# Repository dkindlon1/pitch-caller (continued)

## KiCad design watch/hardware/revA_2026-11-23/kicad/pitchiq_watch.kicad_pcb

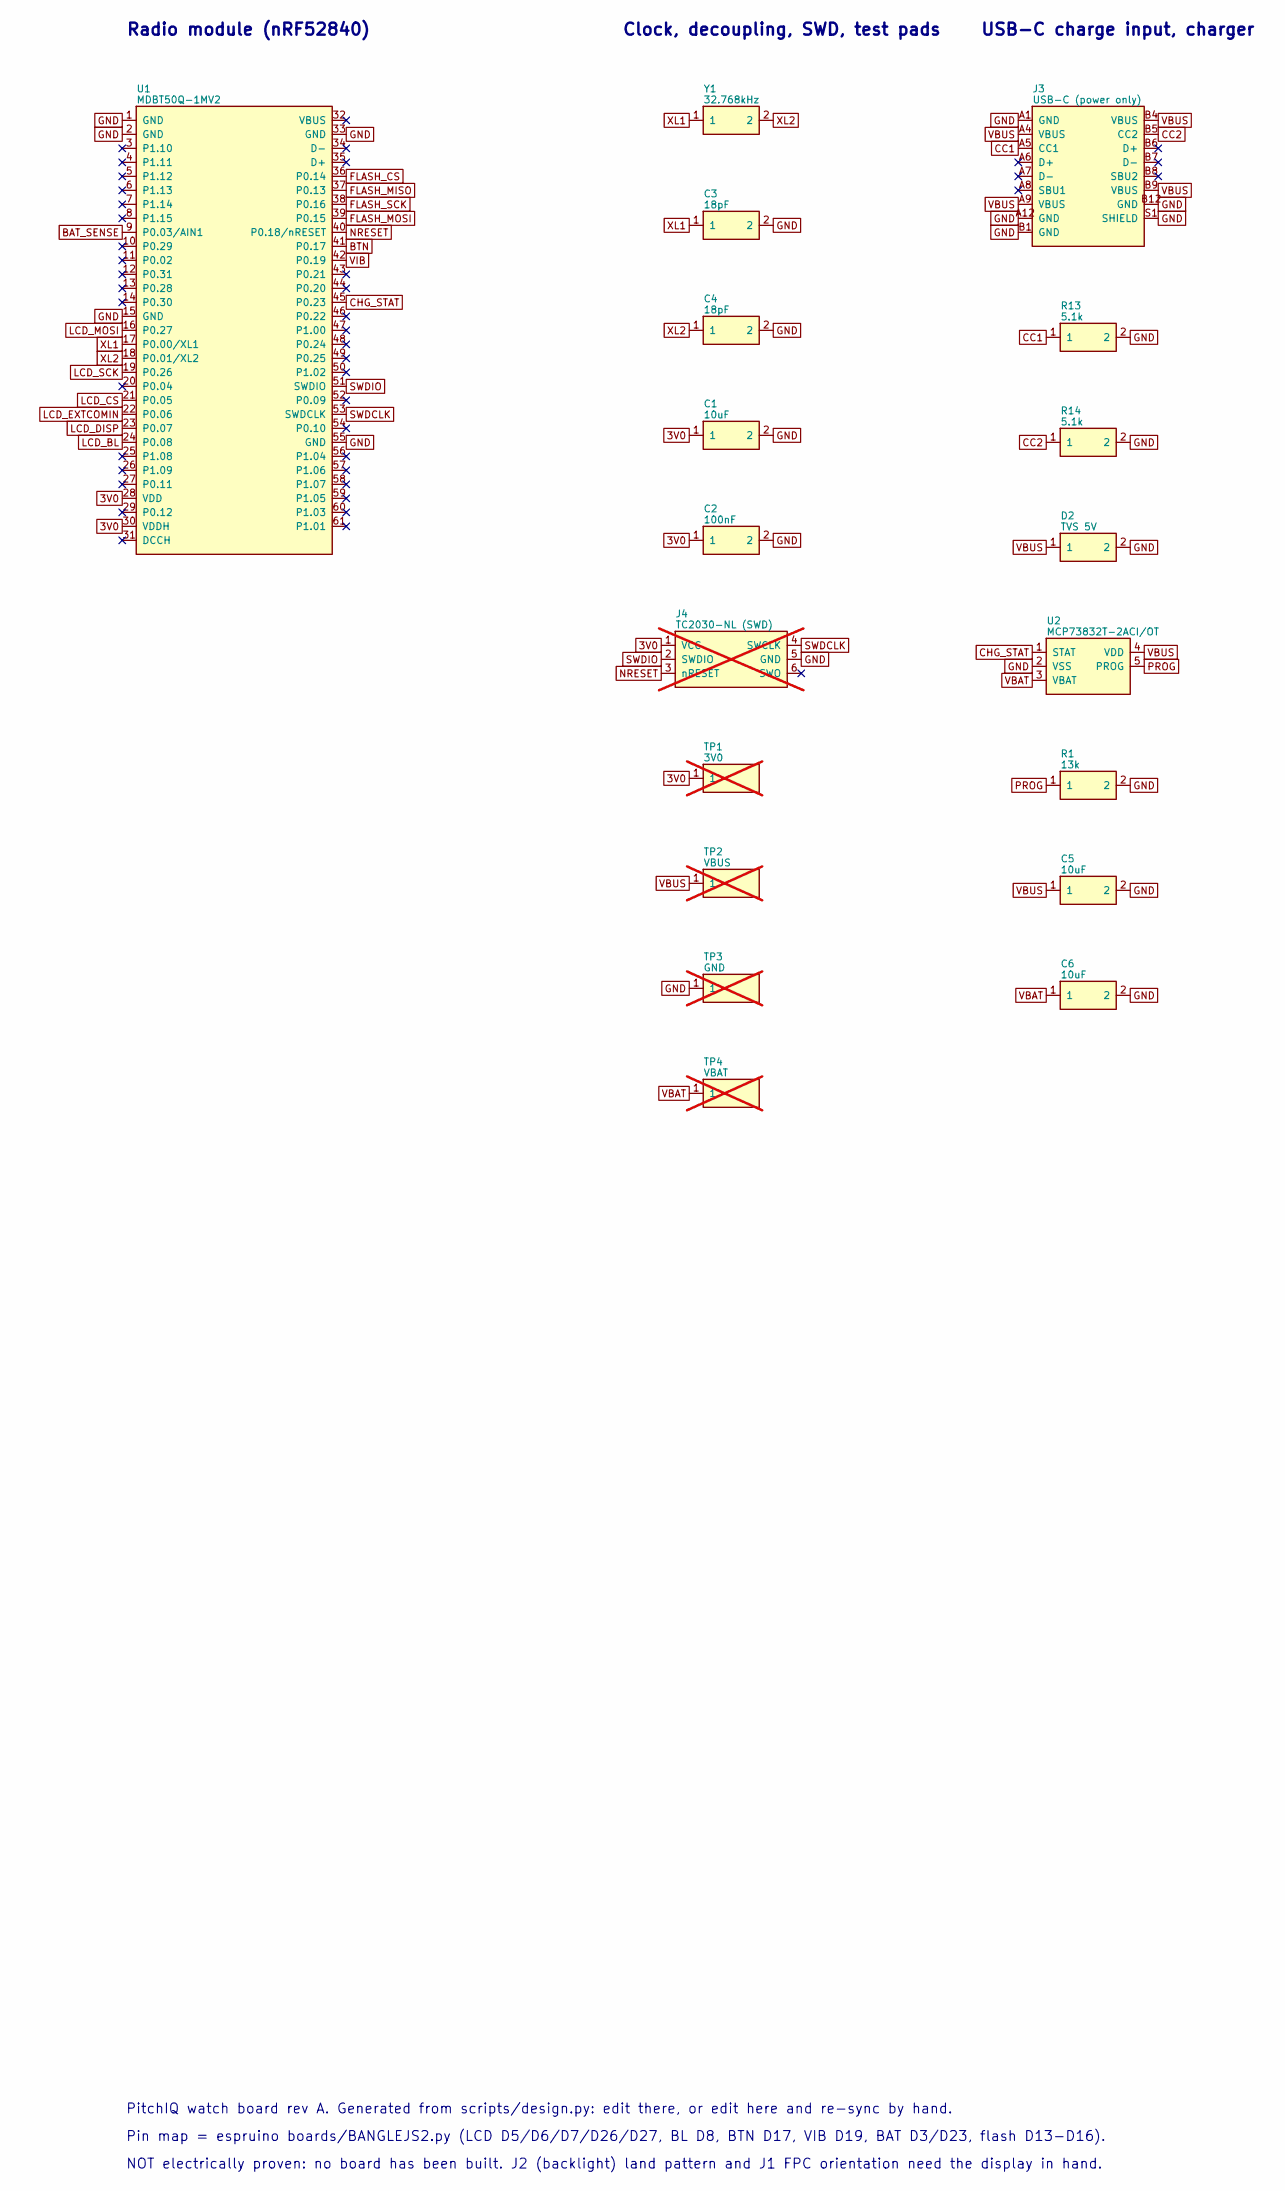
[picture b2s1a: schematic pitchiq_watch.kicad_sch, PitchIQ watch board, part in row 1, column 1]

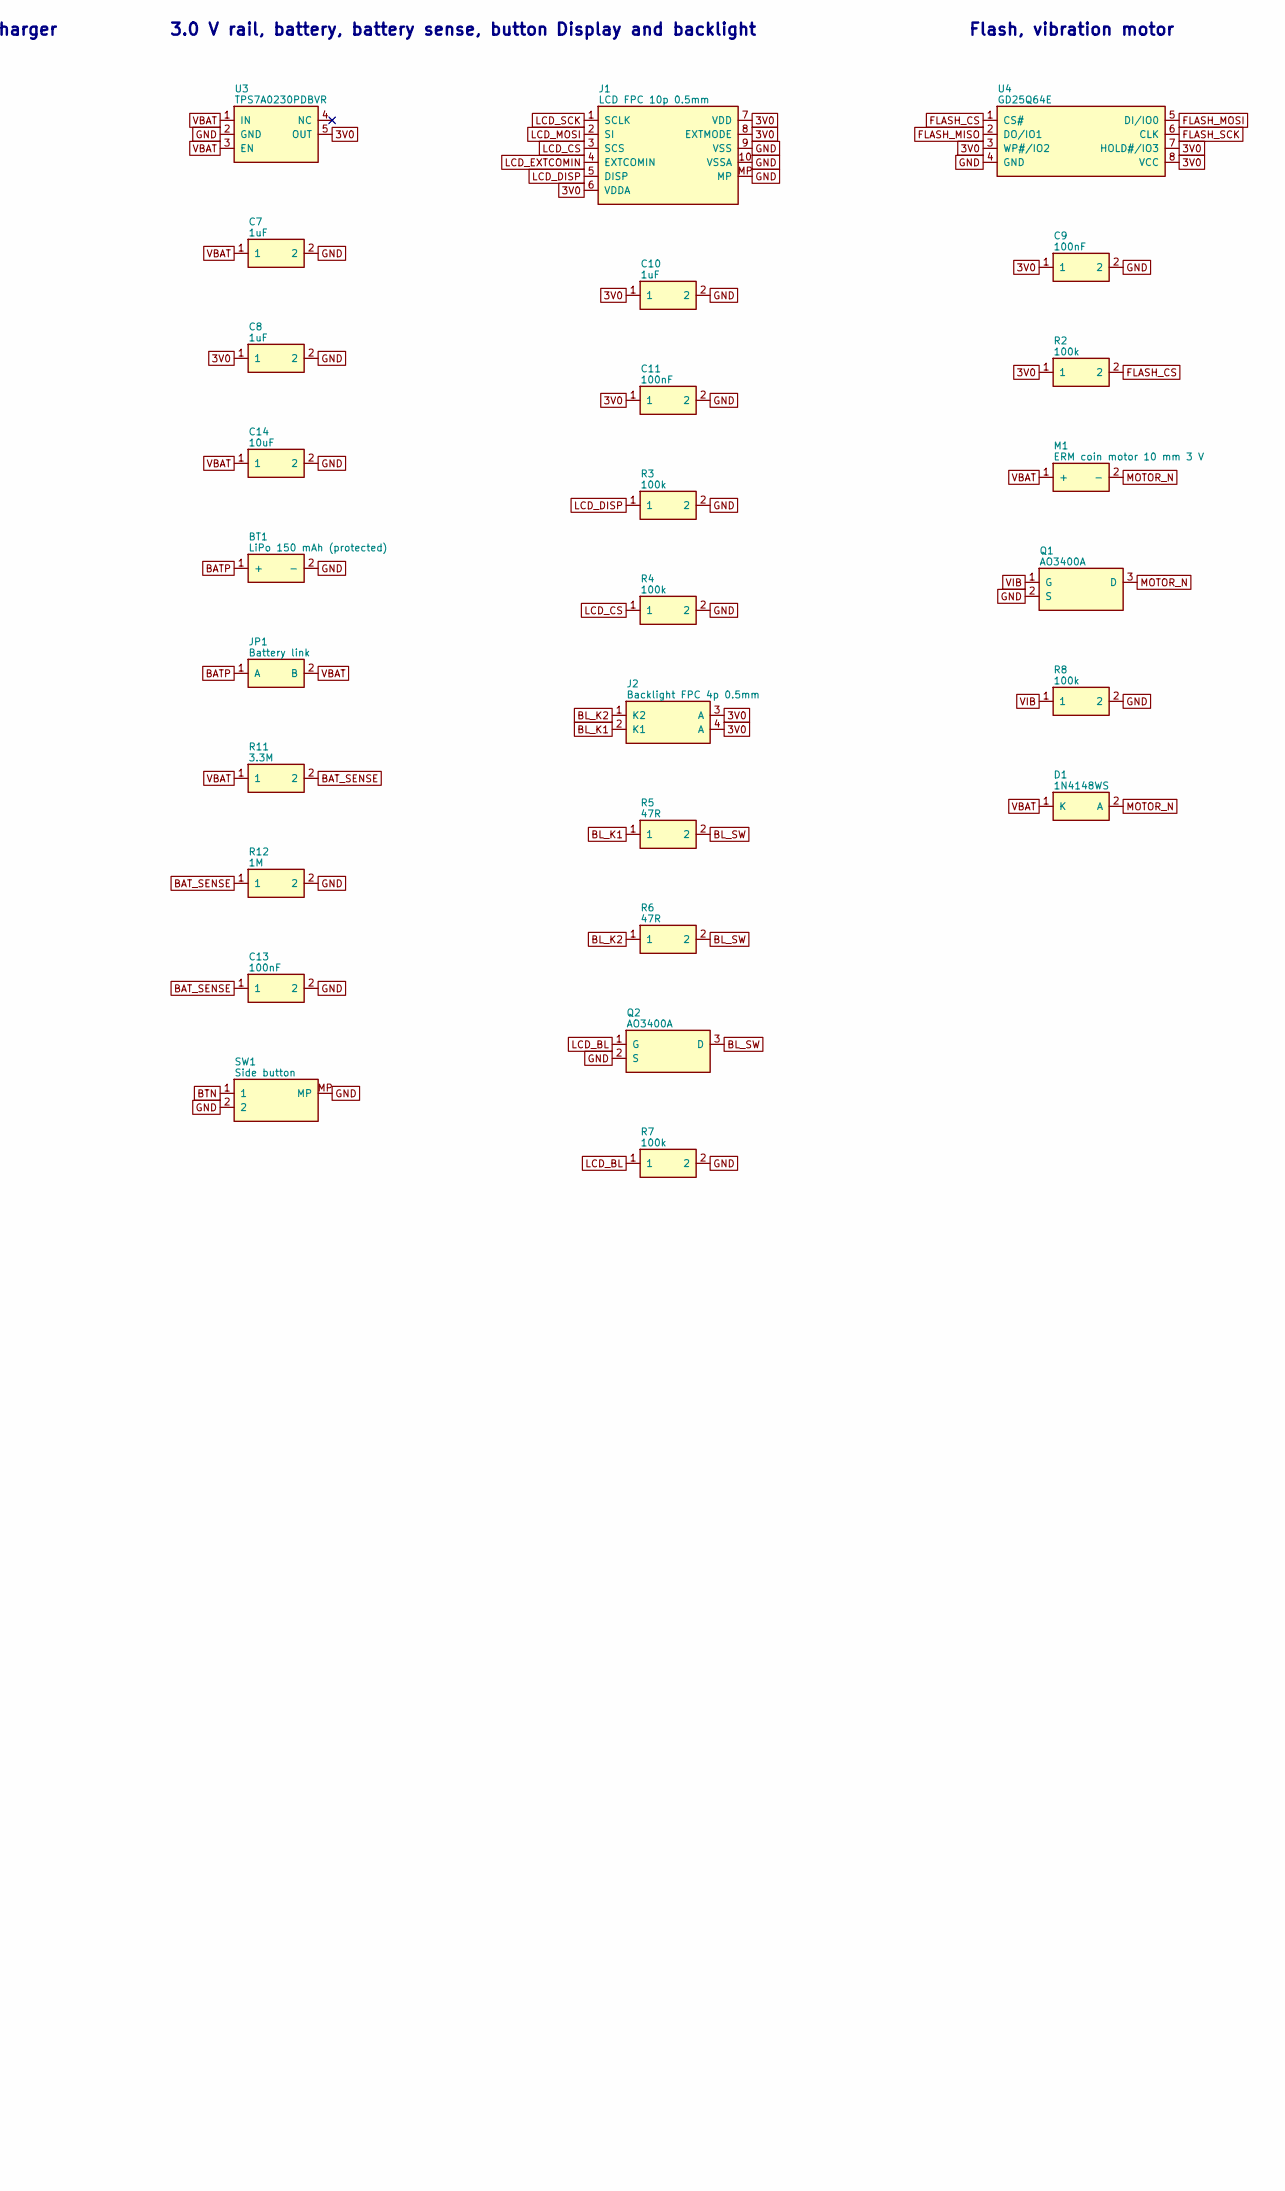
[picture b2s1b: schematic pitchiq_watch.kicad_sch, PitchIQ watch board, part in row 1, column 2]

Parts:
BT1: LiPo 150 mAh (protected); Pad_2x_wire; MPN 1317
C1, C5, C6, C14: 10uF; C_0603_1608Metric; MPN CL10A106KP8NNNC; LCSC C19702
C2, C9, C11, C13: 100nF; C_0402_1005Metric; MPN CL05B104KO5NNNC; LCSC C1525
C3, C4: 18pF; C_0402_1005Metric; MPN CL05C180JB5NNNC; LCSC C307443
C7, C8, C10: 1uF; C_0402_1005Metric; MPN CL05A105KA5NQNC; LCSC C52923
D1: 1N4148WS; D_SOD-323; MPN 1N4148WS; LCSC C2128
D2: TVS 5V; D_SOD-323; MPN PESD5V0S1BA; LCSC C2985486
J1: LCD FPC 10p 0.5mm; Hirose_FH12-10S-0.5SH_1x10-1MP_P0.50mm_Horizontal; MPN FH12-10S-0.5SH(55); LCSC C506791
J2: Backlight FPC 4p 0.5mm; FPC_4p_0.5mm_pads; MPN (pads only)
J3: USB-C (power only); USB_C_Receptacle_HRO_TYPE-C-31-M-12; MPN TYPE-C-31-M-12; LCSC C165948
J4: TC2030-NL (SWD); Tag-Connect_TC2030-IDC-NL_2x03_P1.27mm_Vertical; MPN (footprint only); not fitted
JP1: Battery link; SolderJumper-2_P1.3mm_Open_RoundedPad1.0x1.5mm; MPN (solder bridge)
M1: ERM coin motor 10 mm 3 V; Pad_2x_wire_small; MPN FIT0774
Q1, Q2: AO3400A; SOT-23; MPN AO3400A; LCSC C20917
R1: 13k; R_0402_1005Metric; MPN 0402WGF1302TCE; LCSC C25754
R2, R3, R4, R7, R8: 100k; R_0402_1005Metric; MPN 0402WGF1003TCE; LCSC C25741
R5, R6: 47R; R_0402_1005Metric; MPN 0402WGF470JTCE; LCSC C25118
R11: 3.3M; R_0402_1005Metric; MPN RC0402FR-073M3L; LCSC C470023
R12: 1M; R_0402_1005Metric; MPN 0402WGF1004TCE; LCSC C26083
R13, R14: 5.1k; R_0402_1005Metric; MPN 0402WGF5101TCE; LCSC C25905
SW1: Side button; SW_Push_1P1T-MP_NO_Horizontal_Alps_SKRTLAE010; MPN SKRTLAE010; LCSC C110293
TP1: 3V0; TestPoint_Pad_D1.5mm; not fitted
TP2: VBUS; TestPoint_Pad_D1.5mm; not fitted
TP3: GND; TestPoint_Pad_D1.5mm; not fitted
TP4: VBAT; TestPoint_Pad_D1.5mm; not fitted
U1: MDBT50Q-1MV2; Raytac_MDBT50Q; MPN MDBT50Q-1MV2; LCSC C5118826
U2: MCP73832T-2ACI/OT; SOT-23-5; MPN MCP73832T-2ACI/OT; LCSC C38066
U3: TPS7A0230PDBVR; SOT-23-5; MPN TPS7A0230PDBVR; LCSC C3747031
U4: GD25Q64E; SOIC-8_5.23x5.23mm_P1.27mm; MPN GD25Q64ESIG; LCSC C2685734
Y1: 32.768kHz; Crystal_SMD_3215-2Pin_3.2x1.5mm; MPN Q13FC13500004; LCSC C32346

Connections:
3V0: C1.1, C2.1, C8.1, C9.1, C10.1, C11.1, J1.6 (VDDA), J1.7 (VDD), J1.8 (EXTMODE), J2.3 (A), J2.4 (A), J4.1 (VCC), R2.1, TP1.1, U1.28 (VDD), U1.30 (VDDH), U3.5 (OUT), U4.3 (WP#/IO2), U4.7 (HOLD#/IO3), U4.8 (VCC)
BATP: BT1.1 (+), JP1.1 (A)
BAT_SENSE: C13.1, R11.2, R12.1, U1.9 (P0.03/AIN1)
BL_K1: J2.2 (K1), R5.1
BL_K2: J2.1 (K2), R6.1
BL_SW: Q2.3 (D), R5.2, R6.2
BTN: SW1.1, U1.41 (P0.17)
CC1: J3.A5 (CC1), R13.1
CC2: J3.B5 (CC2), R14.1
CHG_STAT: U1.45 (P0.23), U2.1 (STAT)
FLASH_CS: R2.2, U1.36 (P0.14), U4.1 (CS#)
FLASH_MISO: U1.37 (P0.13), U4.2 (DO/IO1)
FLASH_MOSI: U1.39 (P0.15), U4.5 (DI/IO0)
FLASH_SCK: U1.38 (P0.16), U4.6 (CLK)
GND: BT1.2 (-), C1.2, C2.2, C3.2, C4.2, C5.2, C6.2, C7.2, C8.2, C9.2, C10.2, C11.2, C13.2, C14.2, D2.2, J1.9 (VSS), J1.10 (VSSA), J1.MP, J3.A1 (GND), J3.A12 (GND), J3.B1 (GND), J3.B12 (GND), J3.S1 (SHIELD), J4.5 (GND), Q1.2 (S), Q2.2 (S), R1.2, R3.2, R4.2, R7.2, R8.2, R12.2, R13.2, R14.2, SW1.2, SW1.MP, TP3.1, U1.1 (GND), U1.2 (GND), U1.15 (GND), U1.33 (GND), U1.55 (GND), U2.2 (VSS), U3.2 (GND), U4.4 (GND)
LCD_BL: Q2.1 (G), R7.1, U1.24 (P0.08)
LCD_CS: J1.3 (SCS), R4.1, U1.21 (P0.05)
LCD_DISP: J1.5 (DISP), R3.1, U1.23 (P0.07)
LCD_EXTCOMIN: J1.4 (EXTCOMIN), U1.22 (P0.06)
LCD_MOSI: J1.2 (SI), U1.16 (P0.27)
LCD_SCK: J1.1 (SCLK), U1.19 (P0.26)
MOTOR_N: D1.2 (A), M1.2 (-), Q1.3 (D)
NRESET: J4.3 (nRESET), U1.40 (P0.18/nRESET)
PROG: R1.1, U2.5 (PROG)
SWDCLK: J4.4 (SWCLK), U1.53 (SWDCLK)
SWDIO: J4.2 (SWDIO), U1.51 (SWDIO)
VBAT: C6.1, C7.1, C14.1, D1.1 (K), JP1.2 (B), M1.1 (+), R11.1, TP4.1, U2.3 (VBAT), U3.1 (IN), U3.3 (EN)
VBUS: C5.1, D2.1, J3.A4 (VBUS), J3.A9 (VBUS), J3.B4 (VBUS), J3.B9 (VBUS), TP2.1, U2.4 (VDD)
VIB: Q1.1 (G), R8.1, U1.42 (P0.19)
XL1: C3.1, U1.17 (P0.00/XL1), Y1.1
XL2: C4.1, U1.18 (P0.01/XL2), Y1.2

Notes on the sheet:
Radio module (nRF52840)
Clock, decoupling, SWD, test pads
USB-C charge input, charger
3.0 V rail, battery, battery sense, button
Display and backlight
Flash, vibration motor
PitchIQ watch board rev A. Generated from scripts/design.py: edit there, or edit here and re-sync by hand.
Pin map = espruino boards/BANGLEJS2.py (LCD D5/D6/D7/D26/D27, BL D8, BTN D17, VIB D19, BAT D3/D23, flash D13-D16).
NOT electrically proven: no board has been built. J2 (backlight) land pattern and J1 FPC orientation need the display in hand.

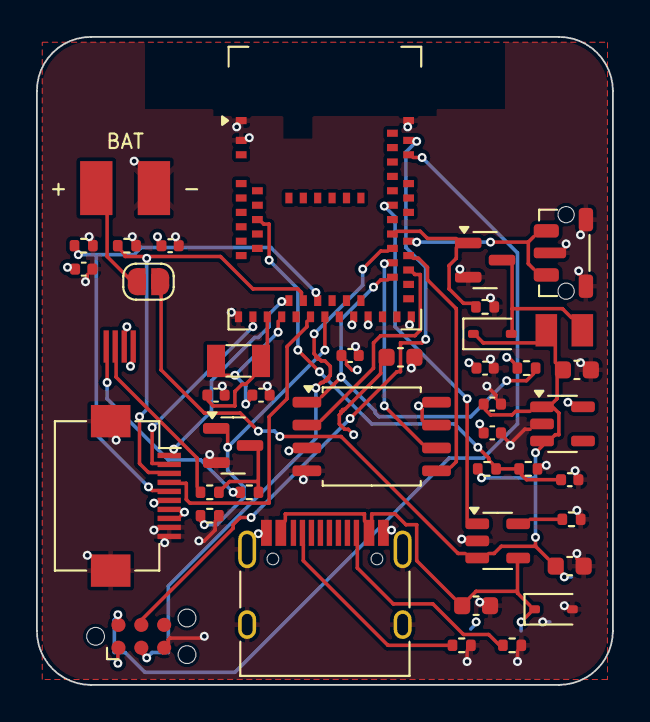
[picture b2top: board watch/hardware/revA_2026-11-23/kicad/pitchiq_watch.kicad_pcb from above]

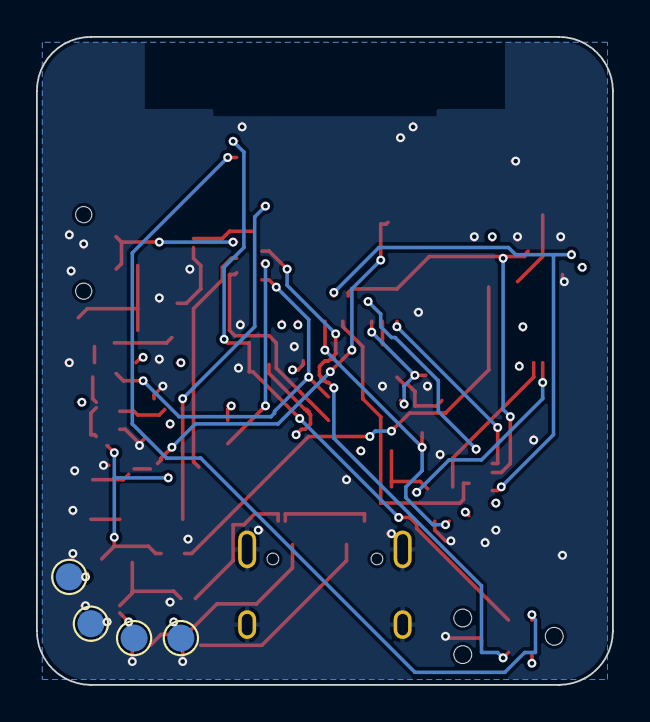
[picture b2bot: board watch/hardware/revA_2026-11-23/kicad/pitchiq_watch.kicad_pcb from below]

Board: 4 copper layers, 32.0 x 36.0 mm, 46 parts (4 on the bottom side), 31 nets.

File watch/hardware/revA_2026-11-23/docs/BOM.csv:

Refs,Qty,Value,Function,Manufacturer,MPN,Footprint,LCSC,Assembly,USD each @1,USD each @~100,Price status,Buy / source
BT1,1,LiPo 150 mAh (protected),3.7 V 150 mAh 402025 cell with protection PCM; leads soldered to pads,Adafruit,1317,Pad_2x_wire,-,hand-soldered after SMT,5.9500,4.7600,seen,https://www.adafruit.com/products/1317
"C1,C5,C6,C14",4,10uF,module bulk decoupling (next to VDD/VDDH pads); charger input; charger output / battery node; battery-rail reservoir for motor start (review finding),Samsung,CL10A106KP8NNNC,C_0603_1608Metric,C19702,SMT,0.0100,0.0030,est (Basic parts seen from $0.0005-0.01),https://www.lcsc.com/product-detail/C19702.html
"C2,C9,C11,C13",4,100nF,module decoupling; flash decoupling; LCD supply; ADC reservoir for the high-impedance divider,Samsung,CL05B104KO5NNNC,C_0402_1005Metric,C1525,SMT,0.0100,0.0030,est (Basic parts seen from $0.0005-0.01),https://www.lcsc.com/product-detail/C1525.html
"C3,C4",2,18pF,crystal load: 2 x (12.5 pF - ~3.5 pF stray),Samsung,CL05C180JB5NNNC,C_0402_1005Metric,C307443,SMT,0.0100,0.0030,est (Basic parts seen from $0.0005-0.01),https://www.lcsc.com/product-detail/C307443.html
"C7,C8,C10",3,1uF,LDO input; LDO output; LCD supply,Samsung,CL05A105KA5NQNC,C_0402_1005Metric,C52923,SMT,0.0100,0.0030,est (Basic parts seen from $0.0005-0.01),https://www.lcsc.com/product-detail/C52923.html
D1,1,1N4148WS,motor flyback diode,various,1N4148WS,D_SOD-323,C2128,SMT,0.0053,0.0053,seen (from-price),https://www.lcsc.com/product-detail/C2128.html
D2,1,TVS 5V,VBUS ESD clamp (bidirectional),DOWO (Nexperia original),PESD5V0S1BA,D_SOD-323,C2985486,SMT,0.0125,0.0125,seen (from-price),https://jlcpcb.com/partdetail/C2985486
J1,1,LCD FPC 10p 0.5mm,"ZIF FPC connector, bottom contact, for LPM013M126 FPC",Hirose,FH12-10S-0.5SH(55),Hirose_FH12-10S-0.5SH_1x10-1MP_P0.50mm_Horizontal,C506791,SMT,0.3016,0.3016,seen (from-price),https://jlcpcb.com/partdetail/HRS_Hirose-FH12_10S_0_5SH_55/C506791
J2,1,Backlight FPC 4p 0.5mm,backlight FPC tail soldered to 4 pads; datasheet connector 503480-0400 is not stocked anywhere found,-,(pads only),FPC_4p_0.5mm_pads,-,hand-soldered after SMT,0.0000,0.0000,n/a,LCSC number not verified: search the MPN
J3,1,USB-C (power only),"USB-C receptacle, charge power only",Korean Hroparts,TYPE-C-31-M-12,USB_C_Receptacle_HRO_TYPE-C-31-M-12,C165948,SMT,0.0975,0.0975,seen (from-price),https://lcsc.com/product-detail/C165948.html
J4,1,TC2030-NL (SWD),pogo footprint for TC2030-IDC-NL cable; no part fitted,Tag-Connect,(footprint only),Tag-Connect_TC2030-IDC-NL_2x03_P1.27mm_Vertical,-,DNP (not fitted),0.0000,0.0000,n/a,LCSC number not verified: search the MPN
JP1,1,Battery link,open until final assembly: isolates the cell while motor/display are fitted; bridge with solder last,-,(solder bridge),SolderJumper-2_P1.3mm_Open_RoundedPad1.0x1.5mm,-,hand-soldered after SMT,0.0000,0.0000,n/a,LCSC number not verified: search the MPN
M1,1,ERM coin motor 10 mm 3 V,"coin vibration motor, leads soldered to pads",DFRobot,FIT0774,Pad_2x_wire_small,-,hand-soldered after SMT,0.9900,0.9900,seen,https://www.digikey.com/en/products/detail/dfrobot/FIT0774/14322639
"Q1,Q2",2,AO3400A,"motor low-side switch (VIBRATE active high, PWM); backlight low-side switch (LCD_BL active high, PWM)",Alpha & Omega,AO3400A,SOT-23,C20917,SMT,0.0429,0.0429,seen (from-price),https://jlcpcb.com/partdetail/C20917
R1,1,13k,charge current 1000 V / 13k = 77 mA,UNI-ROYAL,0402WGF1302TCE,R_0402_1005Metric,C25754,SMT,0.0100,0.0030,est (Basic parts seen from $0.0005-0.01),https://www.lcsc.com/product-detail/C25754.html
"R2,R3,R4,R7,R8",5,100k,flash deselected in reset; display off while the MCU is in reset; LCD deselected in reset (SCS is active high); backlight off in reset; motor off in reset,UNI-ROYAL,0402WGF1003TCE,R_0402_1005Metric,C25741,SMT,0.0100,0.0030,est (Basic parts seen from $0.0005-0.01),https://www.lcsc.com/product-detail/C25741.html
"R5,R6",2,47R,backlight LED 1: (3.0-2.67)/47 = 7 mA; backlight LED 2,UNI-ROYAL,0402WGF470JTCE,R_0402_1005Metric,C25118,SMT,0.0100,0.0030,est (Basic parts seen from $0.0005-0.01),https://www.lcsc.com/product-detail/C25118.html
R11,1,3.3M,battery divider top (set batFullVoltage 0.3256 in firmware),Yageo,RC0402FR-073M3L,R_0402_1005Metric,C470023,SMT,0.0100,0.0030,est (Basic parts seen from $0.0005-0.01),https://www.lcsc.com/product-detail/C470023.html
R12,1,1M,battery divider bottom,UNI-ROYAL,0402WGF1004TCE,R_0402_1005Metric,C26083,SMT,0.0100,0.0030,est (Basic parts seen from $0.0005-0.01),https://www.lcsc.com/product-detail/C26083.html
"R13,R14",2,5.1k,USB-C sink Rd,UNI-ROYAL,0402WGF5101TCE,R_0402_1005Metric,C25905,SMT,0.0100,0.0030,est (Basic parts seen from $0.0005-0.01),https://www.lcsc.com/product-detail/C25905.html
SW1,1,Side button,"side-push tactile switch to GND (BTN1; firmware enables the internal pull-up, jshardware.c 1209-1211)",Alps Alpine,SKRTLAE010,SW_Push_1P1T-MP_NO_Horizontal_Alps_SKRTLAE010,C110293,SMT,0.0744,0.0744,seen (from-price),https://www.lcsc.com/product-detail/C110293.html
TP1,1,3V0,test pad 3V0,,,TestPoint_Pad_D1.5mm,-,DNP (not fitted),0.0000,0.0000,n/a,LCSC number not verified: search the MPN
TP2,1,VBUS,test pad VBUS,,,TestPoint_Pad_D1.5mm,-,DNP (not fitted),0.0000,0.0000,n/a,LCSC number not verified: search the MPN
TP3,1,GND,test pad GND,,,TestPoint_Pad_D1.5mm,-,DNP (not fitted),0.0000,0.0000,n/a,LCSC number not verified: search the MPN
TP4,1,VBAT,test pad VBAT,,,TestPoint_Pad_D1.5mm,-,DNP (not fitted),0.0000,0.0000,n/a,LCSC number not verified: search the MPN
U1,1,MDBT50Q-1MV2,"nRF52840 BLE module, chip antenna, FCC ID SH6MDBT50Q (LCSC out of stock Nov 23: consign)",Raytac,MDBT50Q-1MV2,Raytac_MDBT50Q,C5118826,SMT,8.9500,8.0600,"seen (SparkFun WRL-21605, in stock; DigiKey listing ended, LCSC out of stock)",https://www.sparkfun.com/nordic-nrf52840-ble-module-mdbt50q-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
U2,1,MCP73832T-2ACI/OT,"Li-ion charger 4.20 V, open-drain STAT",Microchip,MCP73832T-2ACI/OT,SOT-23-5,C38066,SMT,0.6635,0.4509,seen,https://www.lcsc.com/product-detail/C38066.html
U3,1,TPS7A0230PDBVR,"3.0 V 200 mA LDO, 25-60 nA quiescent",Texas Instruments,TPS7A0230PDBVR,SOT-23-5,C3747031,SMT,0.2097,0.2097,seen (from-price),https://www.lcsc.com/product-detail/C3747031.html
U4,1,GD25Q64E,"8 MB SPI NOR flash (Espruino Storage), same family as Bangle.js 2",GigaDevice,GD25Q64ESIG,SOIC-8_5.23x5.23mm_P1.27mm,C2685734,SMT,1.1517,0.5475,seen,https://www.lcsc.com/product-detail/C2685734.html
Y1,1,32.768kHz,"FC-135 32.768 kHz 12.5 pF, low-frequency clock (ESPR_LSE_ENABLE)",Epson,Q13FC13500004,Crystal_SMD_3215-2Pin_3.2x1.5mm,C32346,SMT,0.0736,0.0736,seen (from-price),https://www.lcsc.com/product-detail/C32346.html
LCD1,1,"JDI LPM013M126A 1.28in 176x176 memory LCD, NO backlight",display (plugs into J1),JDI,LPM013M126A,-,-,plugged in by hand,34.28,34.28,"seen: $34.28 on the international site (JPY 3,960 in Japan), 19 in stock",https://international.switch-science.com/catalog/2858/
